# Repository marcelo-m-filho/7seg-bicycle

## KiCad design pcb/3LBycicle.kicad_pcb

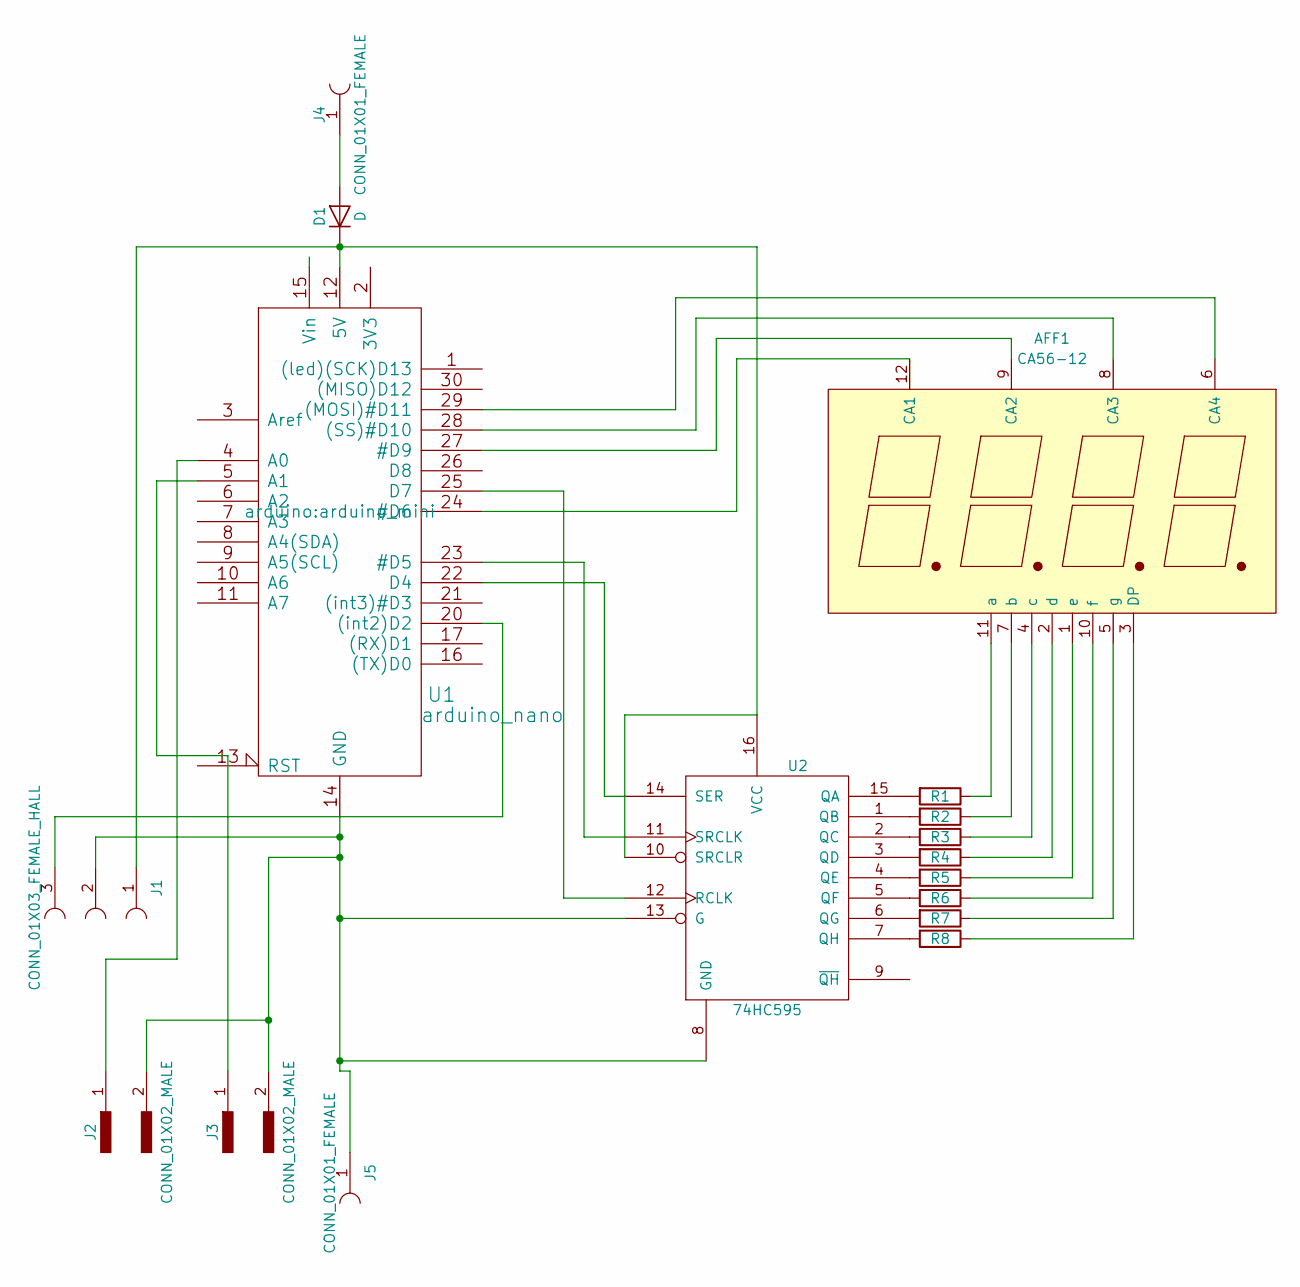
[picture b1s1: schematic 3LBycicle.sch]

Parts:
AFF1: CA56-12; Cx56-12
D1: D; D_A-405_P7.62mm_Horizontal
J1: CONN_01X03_FEMALE_HALL; Pin_Header_Angled_1x03_Pitch2.54mm
J2, J3: CONN_01X02_MALE; Pin_Header_Angled_1x02_Pitch2.54mm
J4, J5: CONN_01X01_FEMALE; Pin_Header_Straight_1x01_Pitch2.54mm
R1, R2, R3, R4, R5, R6, R7, R8: R; R_Axial_DIN0207_L6.3mm_D2.5mm_P7.62mm_Horizontal
U1: arduino_nano; arduino_mini
U2: 74HC595; DIP-16_W7.62mm

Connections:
unnamed: AFF1.1 (e), R5.1
unnamed: AFF1.2 (d), R4.1
unnamed: AFF1.3 (DP), R8.1
unnamed: AFF1.4 (c), R3.1
unnamed: AFF1.5 (g), R7.1
unnamed: AFF1.6 (CA4), U1.29 ((MOSI)#D11)
unnamed: AFF1.7 (b), R2.1
unnamed: AFF1.8 (CA3), U1.28 ((SS)#D10)
unnamed: AFF1.9 (CA2), U1.27 (#D9)
unnamed: AFF1.10 (f), R6.1
unnamed: AFF1.11 (a), R1.1
unnamed: AFF1.12 (CA1), U1.24 (#D6)
unnamed: D1.1 (K), J1.1, U1.12 (5V), U2.10 (SRCLR), U2.16 (VCC)
unnamed: D1.2 (A), J4.1
unnamed: J1.2, J2.2, J3.2, J5.1, U1.14 (GND), U2.8 (GND), U2.13 (G)
unnamed: J1.3, U1.20 ((int2)D2)
unnamed: J2.1, U1.4 (A0)
unnamed: J3.1, U1.5 (A1)
unnamed: R1.2, U2.15 (QA)
unnamed: R2.2, U2.1 (QB)
unnamed: R3.2, U2.2 (QC)
unnamed: R4.2, U2.3 (QD)
unnamed: R5.2, U2.4 (QE)
unnamed: R6.2, U2.5 (QF)
unnamed: R7.2, U2.6 (QG)
unnamed: R8.2, U2.7 (QH)
unnamed: U1.22 (D4), U2.14 (SER)
unnamed: U1.23 (#D5), U2.11 (SRCLK)
unnamed: U1.25 (D7), U2.12 (RCLK)

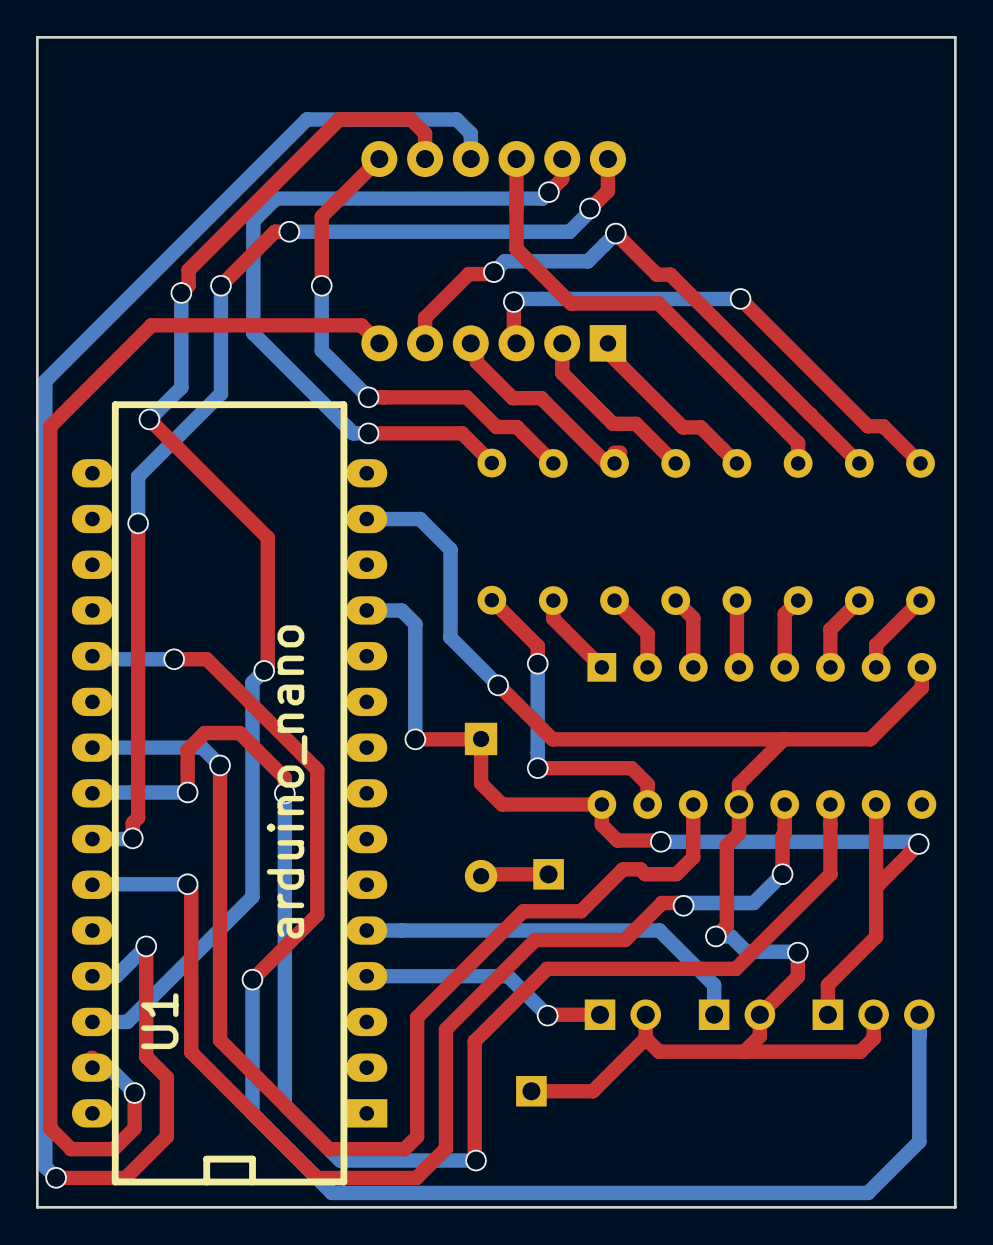
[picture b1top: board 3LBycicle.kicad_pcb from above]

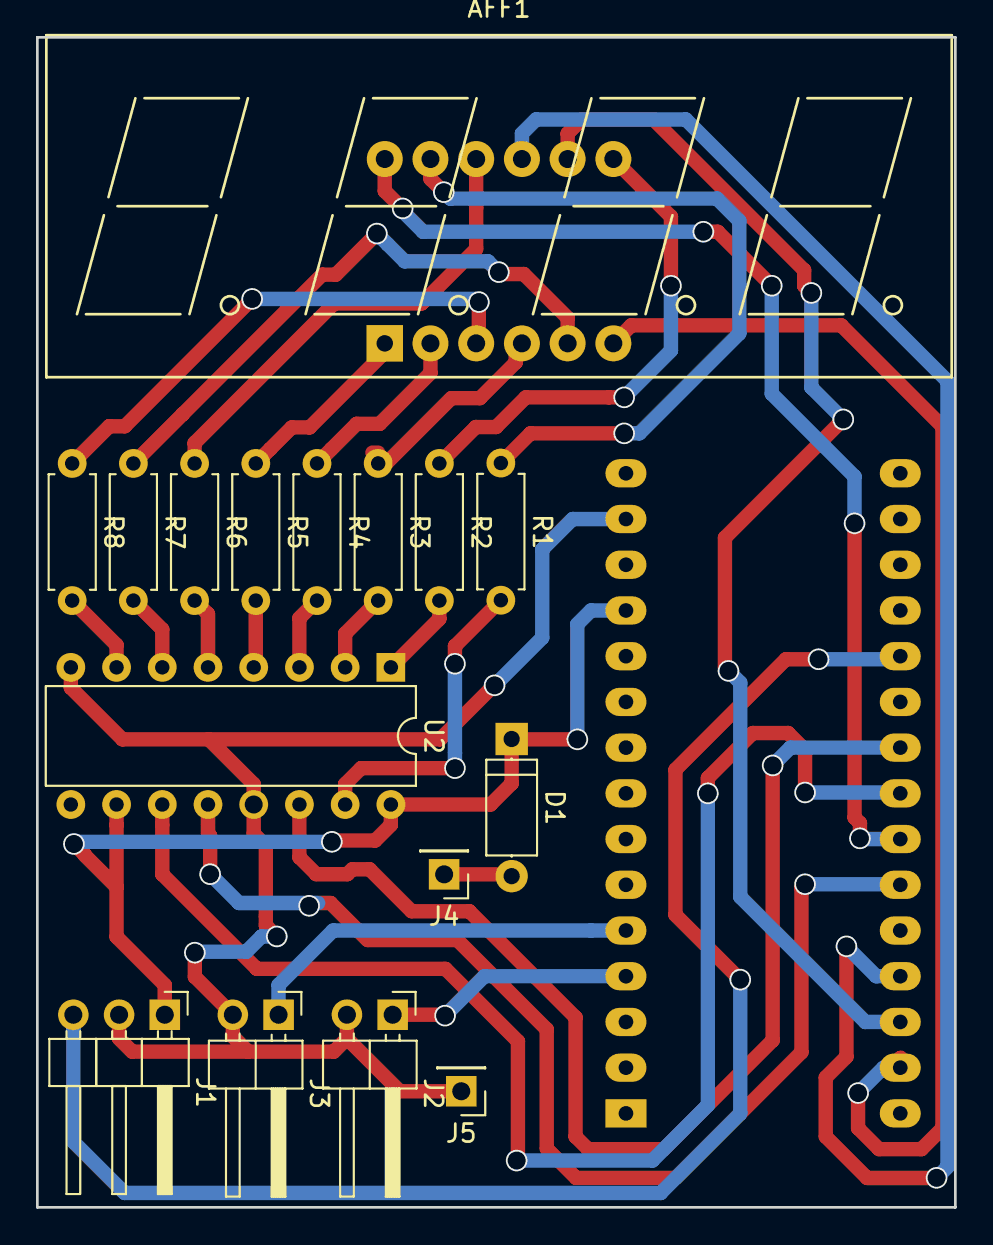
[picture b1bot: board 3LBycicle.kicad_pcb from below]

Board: 2 copper layers, 51.0 x 65.0 mm, 17 parts (16 on the bottom side), 29 nets.

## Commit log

2018-07-11 Initial commit.
